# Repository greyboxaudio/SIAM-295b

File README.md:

# SIAM 295b
This design is based on the Siemens W295b Equalizer.

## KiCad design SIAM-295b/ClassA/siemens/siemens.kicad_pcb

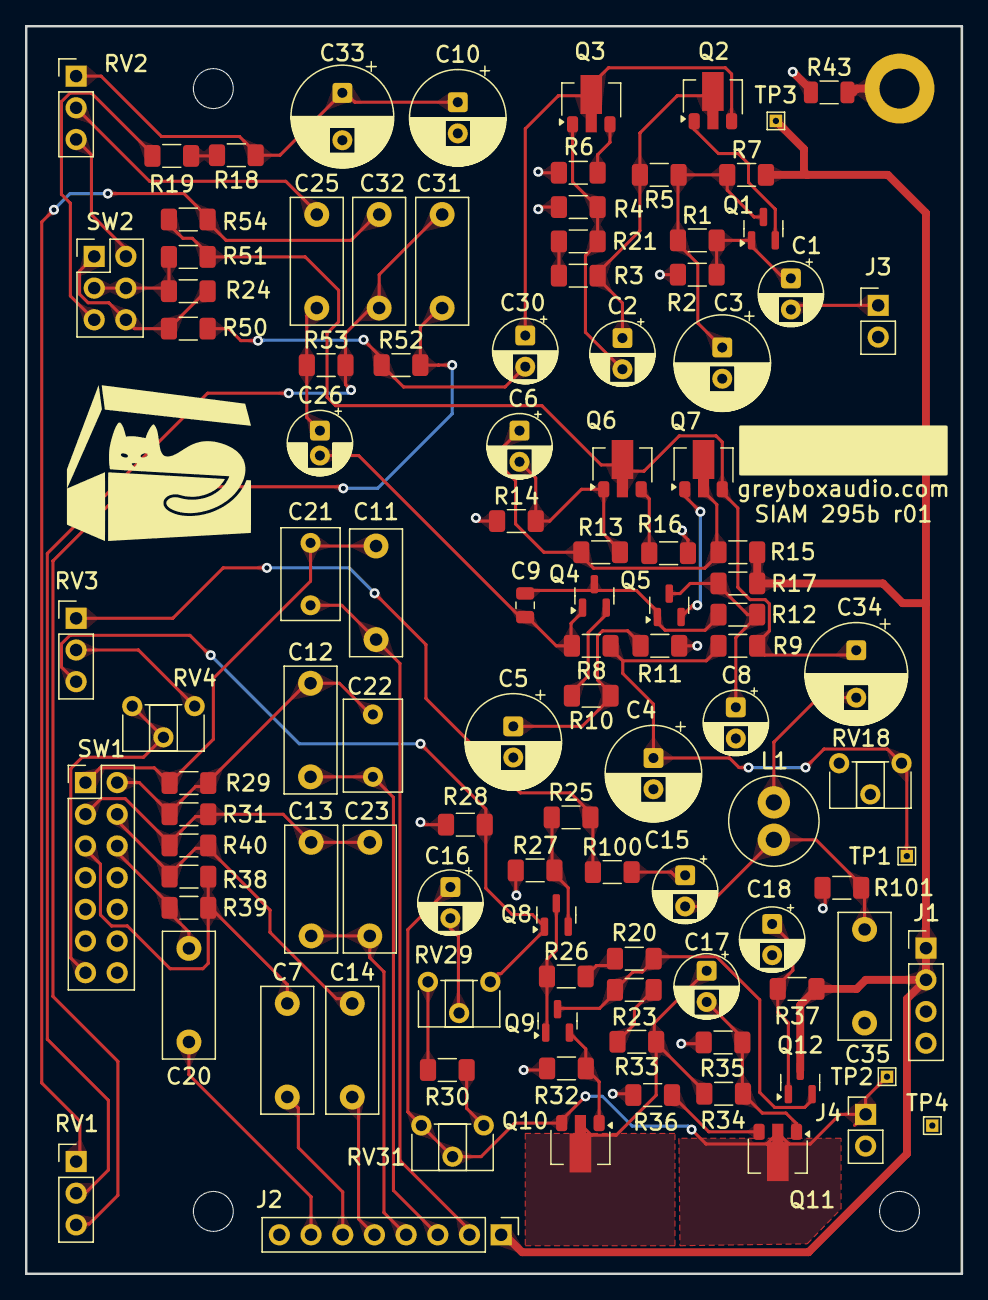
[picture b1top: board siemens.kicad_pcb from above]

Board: 2 copper layers, 75.0 x 100.0 mm, 111 parts (0 on the bottom side), 68 nets.

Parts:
C1, C2, C6: 4u7; CP_Radial_D5.0mm_P2.50mm
C3, C4, C5, C10: 47u; CP_Radial_D7.5mm_P2.50mm
C7: 150n; C_Rect_L10.0mm_W4.0mm_P7.50mm_MKS4
C8, C16, C18, C30: 22u; CP_Radial_D5.0mm_P2.50mm
C9: 47p; C_0805_2012Metric
C11: 22n; C_Rect_L10.0mm_W4.0mm_P7.50mm_MKS4
C12: 33n; C_Rect_L10.0mm_W4.0mm_P7.50mm_MKS4
C13: 47n; C_Rect_L10.0mm_W4.0mm_P7.50mm_MKS4
C14: 100n; C_Rect_L10.0mm_W4.0mm_P7.50mm_MKS4
C15: 33u; CP_Radial_D5.0mm_P2.50mm
C17: 10u; CP_Radial_D5.0mm_P2.50mm
C20: 220n; C_Rect_L10.0mm_W4.0mm_P7.50mm_MKS4
C21, C22: 4n7; C_Rect_L7.2mm_W4.5mm_P5.00mm_FKS2_FKP2_MKS2_MKP2
C23, C25, C35: 10n; C_Rect_L10.0mm_W4.0mm_P7.50mm_MKS4
C26: 4u7; CP_Radial_D5.0mm_P2.00mm
C31, C32: 470n; C_Rect_L10.0mm_W4.0mm_P7.50mm_MKS4
C33, C34: 100u; CP_Radial_D8.0mm_P3.80mm
H1, H2, H4: MountingHole; MountingHole_3.2mm_M3_DIN965
H3: MountingHole; MountingHole_3.2mm_M3_DIN965_Pad
J1: PWR_IN; PinHeader_1x04_P2.54mm_Vertical
J2: Conn_01x08_Pin; PinHeader_1x08_P2.54mm_Vertical
J3: AUDIO_IN; PinHeader_1x02_P2.54mm_Vertical
J4: AUDIO_OUT; PinHeader_1x02_P2.54mm_Vertical
L1: 5m6; L_Radial_D7.0mm_P3.00mm
Q1, Q4, Q5, Q8, Q9, Q12: BC849; SOT-23
Q2, Q3, Q6, Q7, Q10, Q11: BCX56; SOT-89-3
R1: 10k; R_1206_3216Metric_Pad1.30x1.75mm_HandSolder
R2, R25, R34: 12k; R_1206_3216Metric_Pad1.30x1.75mm_HandSolder
R3: 15k; R_1206_3216Metric_Pad1.30x1.75mm_HandSolder
R4, R14, R35: 820R; R_1206_3216Metric_Pad1.30x1.75mm_HandSolder
R5, R6: 30R; R_1206_3216Metric_Pad1.30x1.75mm_HandSolder
R7: 33R; R_1206_3216Metric_Pad1.30x1.75mm_HandSolder
R8: 6k2; R_1206_3216Metric_Pad1.30x1.75mm_HandSolder
R9: 3k9; R_1206_3216Metric_Pad1.30x1.75mm_HandSolder
R10, R17, R19: 100R; R_1206_3216Metric_Pad1.30x1.75mm_HandSolder
R11: 2k; R_1206_3216Metric_Pad1.30x1.75mm_HandSolder
R12: 68k; R_1206_3216Metric_Pad1.30x1.75mm_HandSolder
R13: 20k; R_1206_3216Metric_Pad1.30x1.75mm_HandSolder
R15: 51R; R_1206_3216Metric_Pad1.30x1.75mm_HandSolder
R16: 22R; R_1206_3216Metric_Pad1.30x1.75mm_HandSolder
R18, R30: 2k4; R_1206_3216Metric_Pad1.30x1.75mm_HandSolder
R20, R26: 100k; R_1206_3216Metric_Pad1.30x1.75mm_HandSolder
R21, R37: 1k; R_1206_3216Metric_Pad1.30x1.75mm_HandSolder
R23, R33, R36: 10R; R_1206_3216Metric_Pad1.30x1.75mm_HandSolder
R24, R29, R31, R38, R39, R40: 4M7; R_1206_3216Metric_Pad1.30x1.75mm_HandSolder
R27: 39k; R_1206_3216Metric_Pad1.30x1.75mm_HandSolder
R28, R53: 3k3; R_1206_3216Metric_Pad1.30x1.75mm_HandSolder
R32: 51k; R_1206_3216Metric_Pad1.30x1.75mm_HandSolder
R43: 0R; R_1206_3216Metric
R50, R51: 750R; R_1206_3216Metric_Pad1.30x1.75mm_HandSolder
R52, R54, R100: 1k3; R_1206_3216Metric_Pad1.30x1.75mm_HandSolder
R101: 620R; R_1206_3216Metric_Pad1.30x1.75mm_HandSolder
RV1: 10k; PinHeader_1x03_P2.54mm_Vertical
RV2: 2k5; PinHeader_1x03_P2.54mm_Vertical
RV3: 100k; PinHeader_1x03_P2.54mm_Vertical
RV4, RV18, RV29, RV31: 5k; Potentiometer_ACP_CA6-H2,5_Horizontal
SW1: SW_Rotary_2x6; PinHeader_2x07_P2.54mm_Vertical
SW2: SW_DPDT_x2; PinHeader_2x03_P2.54mm_Vertical
TP1: 1.1V; TestPoint_THTPad_1.0x1.0mm_Drill0.5mm
TP2: TRIM/SYM; TestPoint_THTPad_1.0x1.0mm_Drill0.5mm
TP3: 24V; TestPoint_THTPad_1.0x1.0mm_Drill0.5mm
TP4: GND; TestPoint_THTPad_1.0x1.0mm_Drill0.5mm

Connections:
+24V: J1.1, J1.2, J2.1, Q12.3 (C), R7.2, R15.2, R17.1, R37.1, TP3.1
GND: C3.2, C4.2, C5.2, C8.2, C10.2, C18.2, C33.2, C35.2, J1.3, J1.4, J2.8, J3.2, J4.2, R2.2, R4.1, R6.1, R11.1, R14.1, R16.1, R27.1, R28.1, R32.1, R35.1, R36.1, R43.2, R101.2, RV18.2, RV18.3, TP4.1
unnamed: C4.1, R8.1, R9.1, RV18.1, TP1.1
unnamed: C5.1, R10.1, R11.2
unnamed: C7.1, R38.1, R39.2, SW1.5
unnamed: C10.1, C33.1, R18.1, RV2.1
unnamed: C11.2, C21.2, R29.2, SW1.1
unnamed: C12.1, C22.2, R29.1, R31.2, SW1.2
unnamed: C13.1, C23.2, R31.1, R40.2, SW1.3
unnamed: C14.1, R38.2, R40.1, SW1.4
unnamed: C15.1, R100.2
unnamed: C15.2, C35.1, L1.2, R101.1
unnamed: C16.2, RV29.2
unnamed: C20.1, R39.1, SW1.6
unnamed: C25.1, RV2.2
unnamed: C25.2, C26.1, R53.1
unnamed: C30.2, R50.1, R52.1
unnamed: C31.1, R52.2, RV1.3
unnamed: C31.2, C32.1, R53.2, RV1.2
unnamed: C32.2, R54.2, RV1.1
unnamed: C34.2, L1.1
unnamed: H3.1, R43.1
unnamed: C11.1, C21.1, J2.2
unnamed: C12.2, C22.1, J2.3
unnamed: C13.2, C23.1, J2.4
unnamed: C14.2, J2.5
unnamed: C7.2, J2.6
unnamed: C20.2, J2.7
unnamed: C1.2, J3.1
unnamed: C16.1, J4.1, Q10.3 (E), Q11.2 (C), RV31.2, RV31.3, TP2.1
unnamed: C1.1, Q1.1 (B), R1.2, R2.1
unnamed: C3.1, Q1.3 (C), R1.1, R5.2, R7.1
unnamed: Q1.2 (E), Q2.1 (B)
unnamed: C2.1, Q2.2 (C), R3.2, R5.1
unnamed: C30.1, Q2.3 (E), Q3.2 (C)
unnamed: C2.2, Q3.1 (B), R4.2, R21.1
unnamed: Q3.3 (E), R6.2
unnamed: C9.2, C26.2, Q4.1 (B), R8.2
unnamed: C9.1, Q4.3 (C), Q5.1 (B), R12.1
unnamed: Q4.2 (E), R10.2
unnamed: C8.1, Q5.3 (C), R12.2, R17.2
unnamed: Q5.2 (E), Q7.1 (B)
unnamed: C6.2, Q6.1 (B), R13.2, R14.2
unnamed: C34.1, Q6.2 (C), Q7.3 (E), R9.2, R51.2, R54.1
unnamed: Q6.3 (E), R16.2
unnamed: C6.1, Q7.2 (C), R13.1, R15.1
unnamed: Q8.1 (B), R28.2, RV3.3, RV29.1
unnamed: Q8.3 (C), Q9.1 (B), R26.1
unnamed: Q8.2 (E), R25.1, R27.2
unnamed: Q9.2 (E), Q10.1 (B), R32.2
unnamed: C17.1, Q10.2 (C), R33.1, R34.1
unnamed: C17.2, Q11.1 (B), R34.2, R35.2
unnamed: Q11.3 (E), R36.2
unnamed: C18.1, Q12.1 (B), R37.2
unnamed: Q9.3 (C), Q12.2 (E), R20.2, R23.2
unnamed: R18.2, R19.1
unnamed: R20.1, R26.2
unnamed: R3.1, R21.2
unnamed: R23.1, R33.2
unnamed: R30.1, RV31.1
unnamed: R30.2, RV29.3
unnamed: R25.2, R100.1, RV3.1
unnamed: RV3.2, RV4.1
unnamed: RV4.2, RV4.3, SW1.13
unnamed: R24.1, R50.2, SW2.1 (A), SW2.6 (C)
unnamed: RV2.3, SW2.2 (B)
unnamed: R24.2, R51.1, SW2.3 (C), SW2.4 (A)
unnamed: R19.2, SW2.5 (B)

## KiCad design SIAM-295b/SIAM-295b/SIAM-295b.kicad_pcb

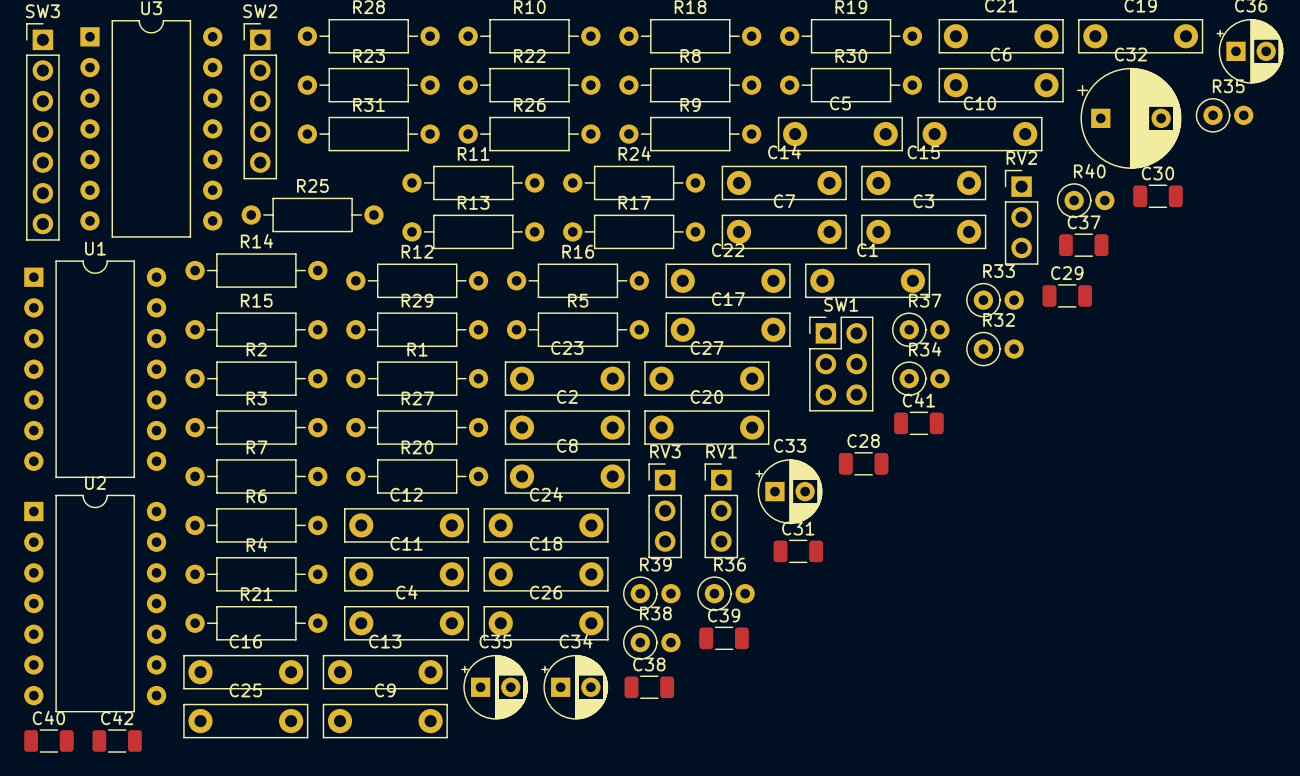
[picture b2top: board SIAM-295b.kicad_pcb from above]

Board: 2 copper layers, 91 parts (0 on the bottom side), 56 nets, no tracks yet.

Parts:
C1, C3, C10: 470n; C_Rect_L10.0mm_W2.5mm_P7.50mm_MKS4
C2, C16, C19, C20: 10n; C_Rect_L10.0mm_W2.5mm_P7.50mm_MKS4
C4, C11, C26: 68n; C_Rect_L10.0mm_W2.5mm_P7.50mm_MKS4
C5: 680n; C_Rect_L10.0mm_W2.5mm_P7.50mm_MKS4
C6, C9, C22: 47n; C_Rect_L10.0mm_W2.5mm_P7.50mm_MKS4
C7: 4n7; C_Rect_L10.0mm_W2.5mm_P7.50mm_MKS4
C8, C13, C27: 2n2; C_Rect_L10.0mm_W2.5mm_P7.50mm_MKS4
C12: 220p; C_Rect_L10.0mm_W2.5mm_P7.50mm_MKS4
C14: 33n; C_Rect_L10.0mm_W2.5mm_P7.50mm_MKS4
C15: 330n; C_Rect_L10.0mm_W2.5mm_P7.50mm_MKS4
C17: 220n; C_Rect_L10.0mm_W2.5mm_P7.50mm_MKS4
C18: 15n; C_Rect_L10.0mm_W2.5mm_P7.50mm_MKS4
C21: 100n; C_Rect_L10.0mm_W2.5mm_P7.50mm_MKS4
C23: 3n3; C_Rect_L10.0mm_W2.5mm_P7.50mm_MKS4
C24: 6n8; C_Rect_L10.0mm_W2.5mm_P7.50mm_MKS4
C25: 22n; C_Rect_L10.0mm_W2.5mm_P7.50mm_MKS4
C28, C29: 100p; C_1206_3216Metric
C30: 220p; C_1206_3216Metric
C31: 22p; C_1206_3216Metric
C32: 150u; CP_Radial_D8.0mm_P5.00mm
C33: 2u2; CP_Radial_D5.0mm_P2.50mm
C34: 22u; CP_Radial_D5.0mm_P2.50mm
C35, C36: 10u; CP_Radial_D5.0mm_P2.50mm
C37, C38, C39, C40, C41, C42: 100n; C_1206_3216Metric
R1, R4, R7: 1k3; R_Axial_DIN0207_L6.3mm_D2.5mm_P10.16mm_Horizontal
R2, R6: 750R; R_Axial_DIN0207_L6.3mm_D2.5mm_P10.16mm_Horizontal
R3, R13: 3k3; R_Axial_DIN0207_L6.3mm_D2.5mm_P10.16mm_Horizontal
R5: 1k2; R_Axial_DIN0207_L6.3mm_D2.5mm_P10.16mm_Horizontal
R8, R9, R11, R12, R15, R16, R18, R19, R20, R23, R24, R26, R27: 1k; R_Axial_DIN0207_L6.3mm_D2.5mm_P10.16mm_Horizontal
R10, R17, R21, R25: 3k; R_Axial_DIN0207_L6.3mm_D2.5mm_P10.16mm_Horizontal
R14: 27k; R_Axial_DIN0207_L6.3mm_D2.5mm_P10.16mm_Horizontal
R22, R28, R29, R30: 10k; R_Axial_DIN0207_L6.3mm_D2.5mm_P10.16mm_Horizontal
R31: 100R; R_Axial_DIN0207_L6.3mm_D2.5mm_P10.16mm_Horizontal
R32, R33, R34, R35, R36, R37, R38, R39, R40: 4M7; R_Axial_DIN0207_L6.3mm_D2.5mm_P2.54mm_Vertical
RV1: 2k5; PinHeader_1x03_P2.54mm_Vertical
RV2, RV3: 10k; PinHeader_1x03_P2.54mm_Vertical
SW1: SW_DPDT_x2; PinHeader_2x03_P2.54mm_Vertical
SW2: SW_Rotary3x4; PinHeader_1x05_P2.54mm_Vertical
SW3: SW_Rotary2x6; PinHeader_1x07_P2.54mm_Vertical
U1, U2, U3: TL074; DIP-14_W10.16mm

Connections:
+12V: C35.1, C37.1, C39.1, C41.1, U1.4 (V+), U2.4 (V+), U3.4 (V+)
-12V: C36.2, C38.1, C40.1, C42.1, U1.11 (V-), U2.11 (V-), U3.11 (V-)
GND: C8.2, C12.2, C28.2, C32.2, C35.2, C36.1, C37.2, C38.2, C39.2, C40.2, C41.2, C42.2, R9.2, R12.2, R16.2, R19.2, R24.2, R27.2, R28.2, U1.5 (+), U1.12 (+)
unnamed: C1.1, C3.1, R3.2, RV3.2
unnamed: C1.2, R1.2, RV3.1
unnamed: C2.1, RV1.2
unnamed: C2.2, C30.1, R3.1, U1.6 (-)
unnamed: C3.2, R7.2, RV3.3
unnamed: C4.1, C7.1, R36.1, SW3.1
unnamed: C4.2, C7.2, R8.1, U2.10 (+)
unnamed: C5.1, C6.1, R8.2, R9.1
unnamed: C5.2, C6.2, U2.8, U2.9 (-)
unnamed: C8.1, R10.1, U2.3 (+)
unnamed: C9.1, R36.2, R37.1, SW3.2
unnamed: C9.2, R11.1, U2.12 (+)
unnamed: C10.1, C11.1, R11.2, R12.1
unnamed: C10.2, C11.2, U2.13 (-), U2.14
unnamed: C12.1, R14.1, U2.5 (+)
unnamed: C13.1, R13.1, R14.2
unnamed: C13.2, R17.2, U2.6 (-), U2.7
unnamed: C14.1, R37.2, R38.1, SW3.3
unnamed: C14.2, R15.1, U3.3 (+)
unnamed: C15.1, R15.2, R16.1
unnamed: C15.2, U3.1, U3.2 (-)
unnamed: C16.1, C19.1, R38.2, R39.1, SW3.4
unnamed: C16.2, C19.2, R18.1, U3.5 (+)
unnamed: C17.1, C18.1, R18.2, R19.1
unnamed: C17.2, C18.2, U3.6 (-), U3.7
unnamed: C20.1, C23.1, R39.2, R40.1, SW3.5
unnamed: C20.2, C23.2, R23.1, U3.10 (+)
unnamed: C21.1, C22.1, R23.2, R24.1
unnamed: C21.2, C22.2, U3.8, U3.9 (-)
unnamed: C24.1, C27.1, R40.2, SW3.6
unnamed: C24.2, C27.2, R26.1, U3.12 (+)
unnamed: C25.1, C26.1, R26.2, R27.1
unnamed: C25.2, C26.2, U3.13 (-), U3.14
unnamed: C28.1, R17.1, RV2.3, U1.10 (+)
unnamed: C29.1, C34.1, R25.1, U1.8
unnamed: C29.2, R25.2, RV2.1, U1.9 (-)
unnamed: C30.2, R6.2, R7.1, R10.2, U1.7
unnamed: C31.1, R29.1, R30.2, U1.13 (-)
unnamed: C31.2, R30.1, R31.2, U1.14
unnamed: C32.1, R4.1, RV1.3
unnamed: C33.2, R28.1, U1.3 (+)
unnamed: C34.2, R29.2
unnamed: R1.1, R2.1, U1.1, U1.2 (-)
unnamed: R2.2, R32.1, SW1.1 (A), SW1.6 (C)
unnamed: R4.2, R5.1
unnamed: R5.2, SW1.5 (B)
unnamed: R13.2, U2.1, U2.2 (-)
unnamed: R20.1, R33.2, R34.1, SW2.2
unnamed: R20.2, R21.2, R22.2, R33.1, SW2.1
unnamed: R21.1, R34.2, R35.1, SW2.3
unnamed: R22.1, R35.2, SW2.4
unnamed: R6.1, R32.2, SW1.3 (C), SW1.4 (A)
unnamed: RV1.1, SW1.2 (B)

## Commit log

2022-03-27 updated schematic
2022-03-29 added Q-Mod circuit, changed project name
2022-03-30 update circuit simulation
2022-08-07 updated schematic
    rev 05
2022-08-07 Rev 05a
    - added a missing OpAmp
    - added a cat
2022-08-08 Rev 05c
    corrected the orientation of several opamps
2022-08-08 update simulation
    changed L2 to 6mH
2022-08-14 housekeeping (Rev05C)
    - corrected missing 10K resistor
    - added output capacitor
    - added annotations
    - changed component numbering to make a little more sense
    - added partial component footprints
2022-08-14 fixed C35/C36 Symbol
    fixed C35/C36 Symbol
2022-08-14 removed redundant 4M7 resistors
2022-09-10 fixed RV1 wiring
2023-01-07 update footprints, started pcb
2024-03-18 updated schematic for kicad 8.0
2024-05-09 updated gyrator design
2024-05-10 update spice sim
2024-05-10 update sim
2024-05-10 update schematic
2024-05-10 moved files
2024-05-10 remove old files
2025-07-11 class A
    added schematic for a THT discrete Class A build (work in progress)
2025-07-11 started pcb
2025-07-12 update pcb
2025-08-16 update pcb
    switch transistors & resistors to smd
2025-08-16 update pcb
    successfully routed all components
2025-08-17 update ocb
    added mounting holes, reduced width
2025-08-17 update & fab
    updated pcb, added fabrication output
2025-08-19 added gyrator circuits
    includes simulation
2025-08-19 updated footprints
2025-08-22 Aktualisieren von README.md
2025-08-25 update pcb
    added thermal realief for Q10/11, increased spacing for larger trim potentiometer footprints
